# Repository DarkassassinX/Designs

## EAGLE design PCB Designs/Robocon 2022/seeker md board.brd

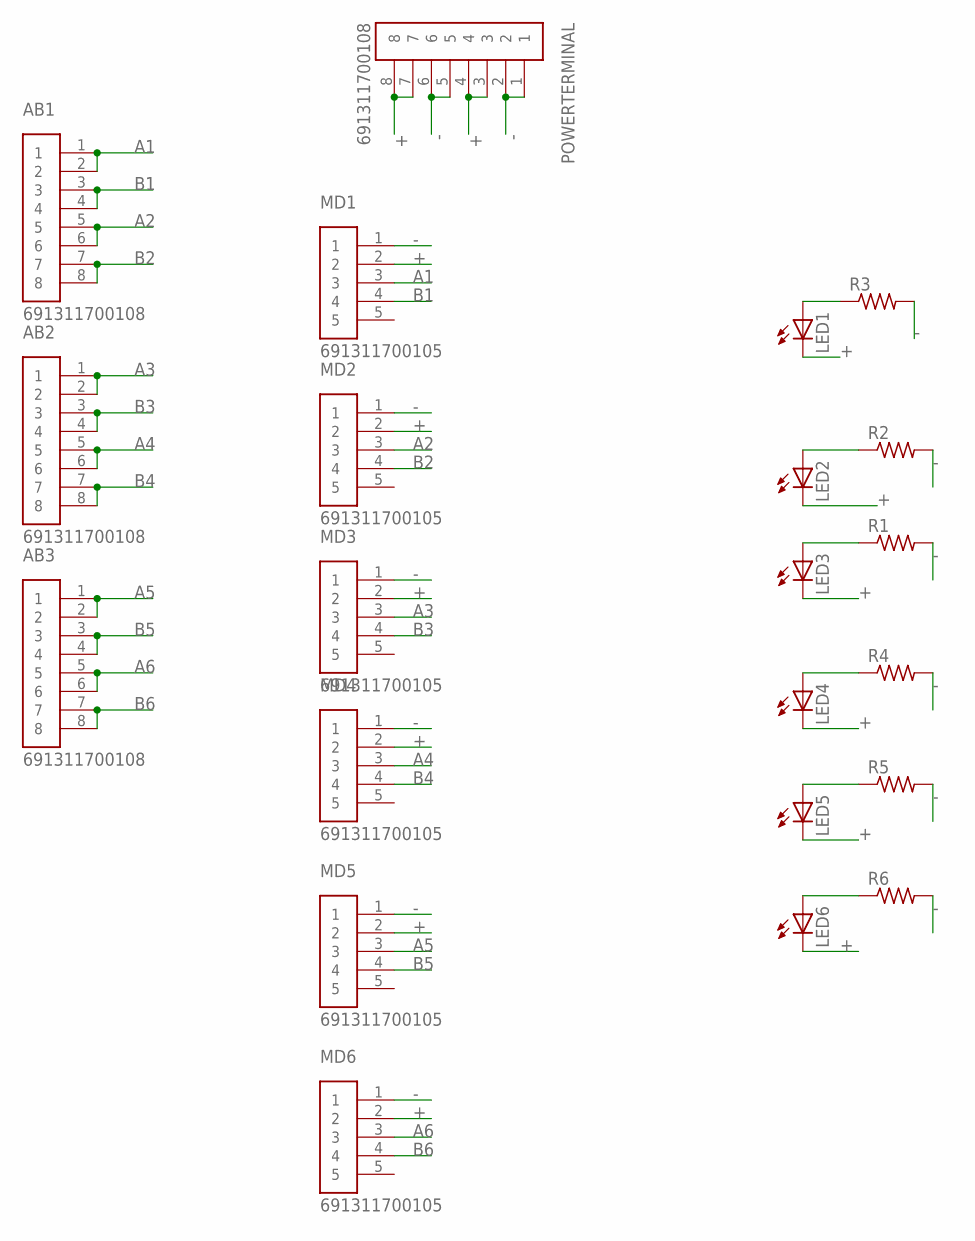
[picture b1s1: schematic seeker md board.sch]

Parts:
AB1, AB2, AB3: 691311700108; TERMINALBLOCK_PLUGGABLE-8-5MM
LED1, LED2, LED3, LED4, LED5, LED6: LEDLZR181; LZR181
MD1, MD2, MD3, MD4, MD5, MD6: 691311700105; TERMINALBLOCK_PLUGGABLE-5-5MM
POWERTERMINAL: 691311700108; TERMINALBLOCK_PLUGGABLE-8-5MM
R1, R2, R3, R4, R5, R6: R-US_0204/5; 0204/5

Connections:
+: LED1.K (C), LED2.K (C), LED3.K (C), LED4.K (C), LED5.K (C), LED6.K (C), MD1.2, MD2.2, MD3.2, MD4.2, MD5.2, MD6.2, POWERTERMINAL.3, POWERTERMINAL.4, POWERTERMINAL.7, POWERTERMINAL.8
-: MD1.1, MD2.1, MD3.1, MD4.1, MD5.1, MD6.1, POWERTERMINAL.1, POWERTERMINAL.2, POWERTERMINAL.5, POWERTERMINAL.6, R1.2, R2.2, R3.2, R4.2, R5.2, R6.2
A1: AB1.1, AB1.2, MD1.3
A2: AB1.5, AB1.6, MD2.3
A3: AB2.1, AB2.2, MD3.3
A4: AB2.5, AB2.6, MD4.3
A5: AB3.1, AB3.2, MD5.3
A6: AB3.5, AB3.6, MD6.3
B1: AB1.3, AB1.4, MD1.4
B2: AB1.7, AB1.8, MD2.4
B3: AB2.3, AB2.4, MD3.4
B4: AB2.7, AB2.8, MD4.4
B5: AB3.3, AB3.4, MD5.4
B6: AB3.7, AB3.8, MD6.4
unnamed: LED1.A, R3.1
unnamed: LED2.A, R2.1
unnamed: LED3.A, R1.1
unnamed: LED4.A, R4.1
unnamed: LED5.A, R5.1
unnamed: LED6.A, R6.1

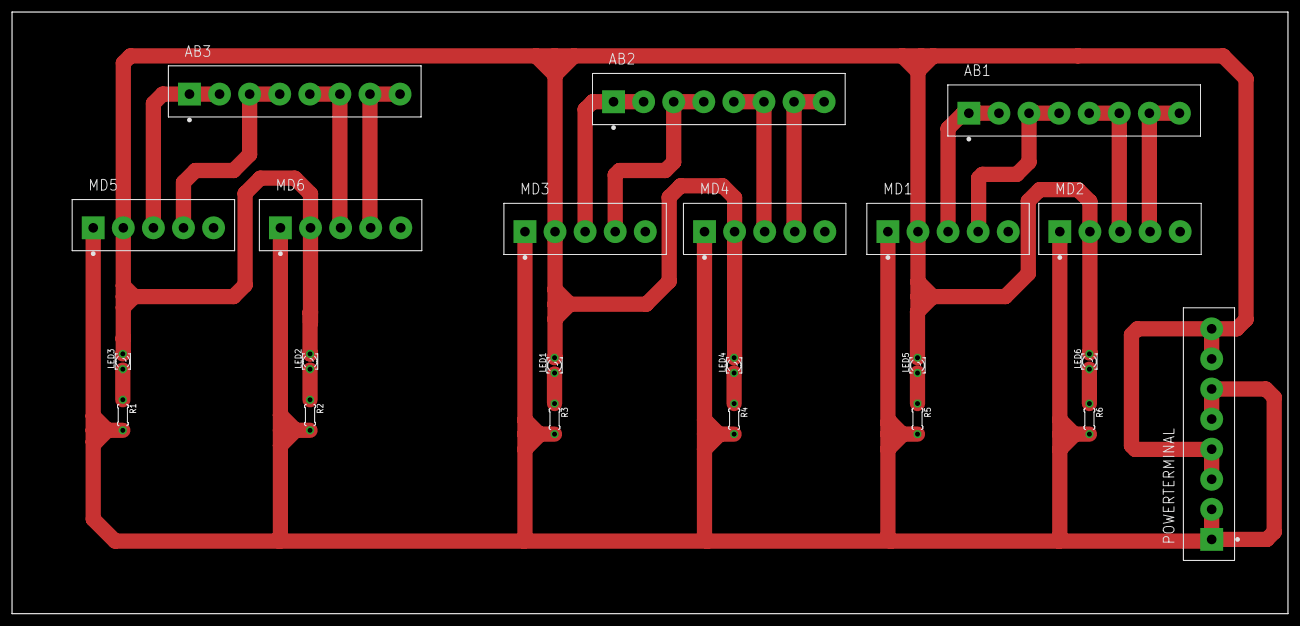
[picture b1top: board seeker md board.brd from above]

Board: 2 copper layers, 212.1 x 100.0 mm, 22 parts (0 on the bottom side), 20 nets.

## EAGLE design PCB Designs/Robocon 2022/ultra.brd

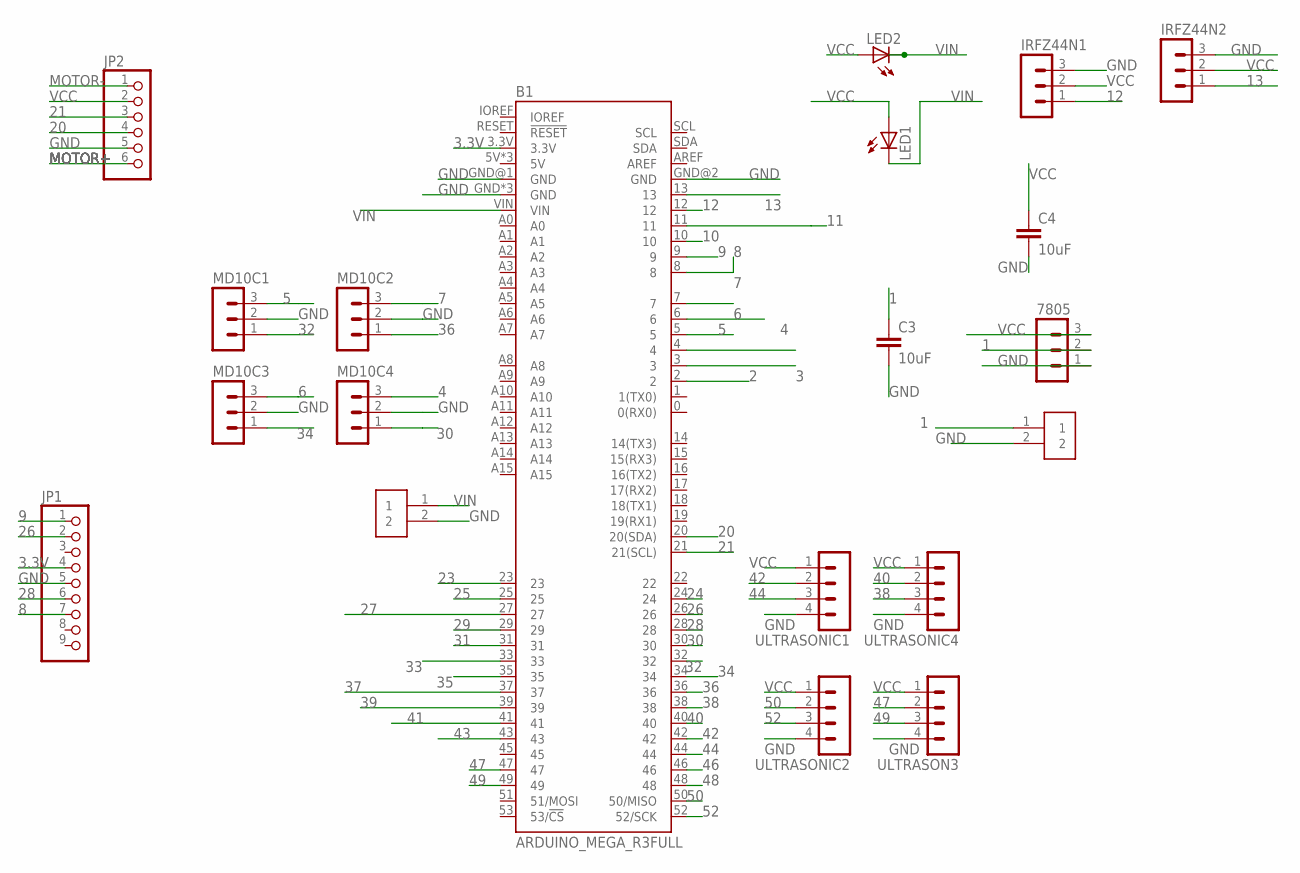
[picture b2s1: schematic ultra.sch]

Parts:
7805: MA03-1
B1: ARDUINO_MEGA_R3FULL; ARDUINO_MEGA_NO_SILK
C3, C4: 10uF; 0402-TIGHT
IRFZ44N1, IRFZ44N2: MA03-1
J1, J2: 691311400102; TERMINALBLOCK_PLUGGABLE-2-7.62MM
JP1: PINHD-1X9; 1X09-BIG
JP2: PINHD-1X6; 1X06
LED1, LED2: LED; SMARTLED-TTW
MD10C1, MD10C2, MD10C3, MD10C4: MA03-1
ULTRASON3: MA04-1
ULTRASONIC1, ULTRASONIC2, ULTRASONIC4: MA04-1

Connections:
1: 7805.2, C3.1, J2.1
2: B1.2
3: B1.3
3.3V: B1.3.3V, JP1.4
4: B1.4, MD10C4.3
5: B1.5, MD10C1.3
6: B1.6, MD10C3.3
7: B1.7, MD10C2.3
8: B1.8, JP1.7
9: B1.9, JP1.1
10: B1.10
11: B1.11
12: B1.12, IRFZ44N1.1
13: B1.13, IRFZ44N2.1
20: B1.20 (20(SDA)), JP2.4
21: B1.21 (21(SCL)), JP2.3
23: B1.23
24: B1.24
25: B1.25
26: B1.26, JP1.2
27: B1.27
28: B1.28, JP1.6
29: B1.29
30: B1.30, MD10C4.1
31: B1.31
32: B1.32, MD10C1.1
33: B1.33
34: B1.34, MD10C3.1
35: B1.35
36: B1.36, MD10C2.1
37: B1.37
38: B1.38, ULTRASONIC4.3
39: B1.39
40: B1.40, ULTRASONIC4.2
41: B1.41
42: B1.42, ULTRASONIC1.2
43: B1.43
44: B1.44, ULTRASONIC1.3
46: B1.46
47: B1.47, ULTRASON3.2
48: B1.48
49: B1.49, ULTRASON3.3
50: B1.50 (50/MISO), ULTRASONIC2.2
52: B1.52 (52/SCK), ULTRASONIC2.3
GND: 7805.1, B1.GND, B1.GND@1 (GND), B1.GND@2 (GND), B1.GND@3 (GND), B1.GND@4 (GND), C3.2, C4.2, IRFZ44N1.3, IRFZ44N2.3, J1.2, J2.2, JP1.5, JP2.5, MD10C1.2, MD10C2.2, MD10C3.2, MD10C4.2, ULTRASON3.4, ULTRASONIC1.4, ULTRASONIC2.4, ULTRASONIC4.4
MOTOR+: JP2.6
MOTOR-: JP2.1
VCC: 7805.3, C4.1, IRFZ44N1.2, IRFZ44N2.2, JP2.2, LED1.A@1 (A), LED2.A@1 (A), ULTRASON3.1, ULTRASONIC1.1, ULTRASONIC2.1, ULTRASONIC4.1
VIN: B1.VIN, J1.1, LED1.C@1 (C), LED2.C@1 (C)

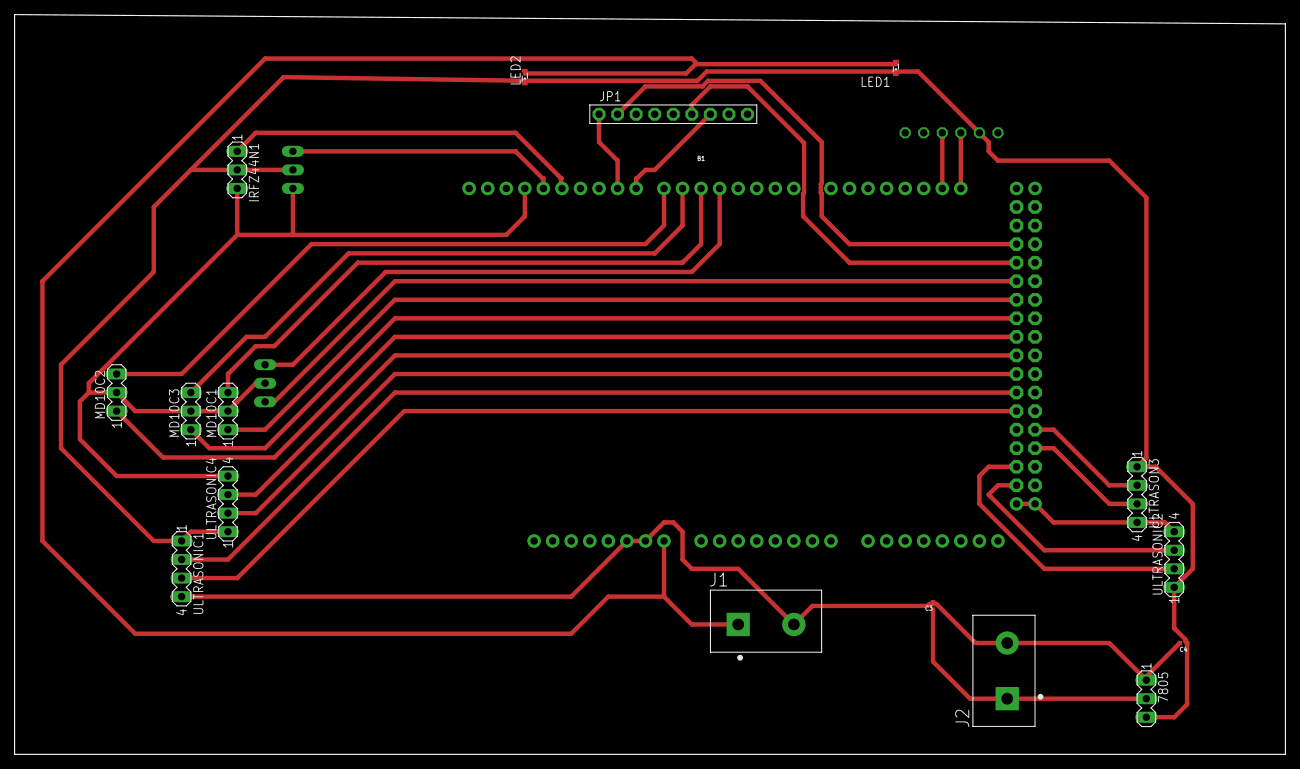
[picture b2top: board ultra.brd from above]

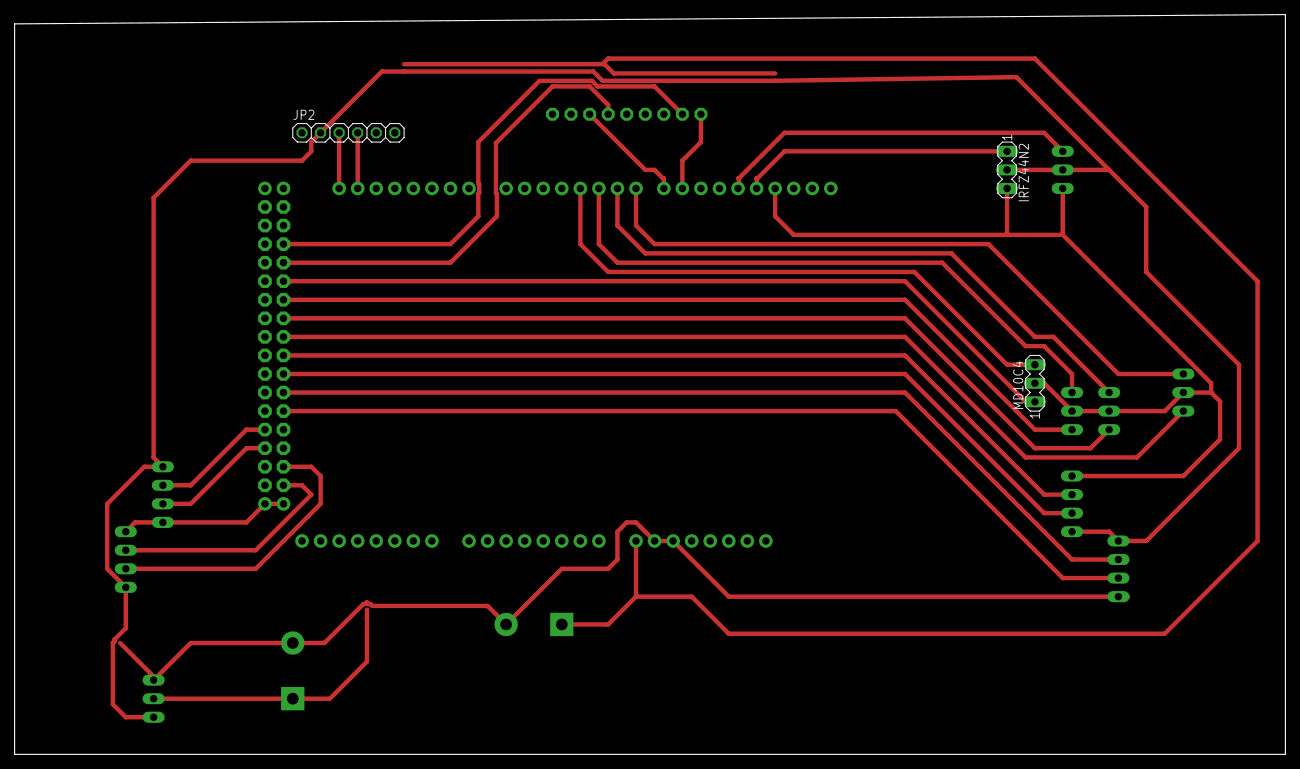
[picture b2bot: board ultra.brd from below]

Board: 2 copper layers, 174.0 x 101.3 mm, 20 parts (3 on the bottom side), 29 nets.

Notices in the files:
parts and their libraries:
SparkFun-Boards: Licensing: Creative Commons ShareAlike 4.0 International - https://creativecommons.org/licenses/by-sa/4.0
